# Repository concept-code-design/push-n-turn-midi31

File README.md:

# Push-n-Turn 31

Push-n-Turn 31 is a USB MIDI controller with 3 keyboard switches (RedDragon low profile), a rotary encoder and 3/4 RGB leds (WS8212).

The device sports a USB type-C connector and requires no device drivers on Mac or PC.

The keys can be configured (via MIDI messages, or the configurator) to produce notes, CC codes (momentary or toggle mode). The encoder produces 0..127 on a configurable CC channel. The encoder button produces 127/0 on a CC channel of choice.
Each switch has an RGB led that shows the state of the switch.
The device uses a modified midi library for CH55x devices made by mi:muz 

## Configuring the keys
Configuration of the keys can be done by sending midi codes to the device.
You can use python midiutil for this (https://github.com/sourcebox/midiutil).

start prog
./midiutil.py -d 1 -w 186 102 42

end prog
./midiutil.py -d 1 -w 186 102 43

module type
./midiutil.py -d 1 -w 186 102 44
returns: (10, 103, INSTRUMENT_TYPE);

firmware version
./midiutil.py -d 1 -w 186 102 45
returns (10, 104, FW_VERSION) 10 for version 1.0

show configuration
./midiutil.py -d 1 -w 186 102 46
returns the config of each of the 6 buttons, the rotary knob and rotary encoder

show stepsize 
./midiutil.py -d 1 -w 186 102 47
returns (10, 105, encStepSize)

show MIDI channel 
./midiutil.py -d 1 -w 186 102 48
returns (10, 106, MIDIChannel)

reboot in firmware update mode
./midiutil.py -d 1 -w 186 102 49

programming keys
./midiutil.py -d 1 -w 186 102 42
./midiutil.py -d 1 -w 186 11 60
./midiutil.py -d 1 -w 186 22 30
./midiutil.py -d 1 -w 186 33 9
./midiutil.py -d 1 -w 186 24 15
./midiutil.py -d 1 -w 186 5 24
./midiutil.py -d 1 -w 186 102 43

## Links & References

* [mi:muz:ch55x Tiny USB MIDI Library for Ch55xduino](https://github.com/mimuz/mimuz-ch55x)
* [push-n-turn-midi61](https://github.com/concept-code-design/push-n-turn-midi61)

# License

Concept & Code invests time and resources providing this open source design, please support them and open-source hardware by purchasing products from Etsy or Tindie!

Designed by Ronald Leenes.

Firmware released under an GNU AGPL v3.0 license. See the LICENSE file for more information.

Hardware released under an CERN Open Hardware Licence v1.2. See the LICENSE_HARDWARE file for more information.

February 2025

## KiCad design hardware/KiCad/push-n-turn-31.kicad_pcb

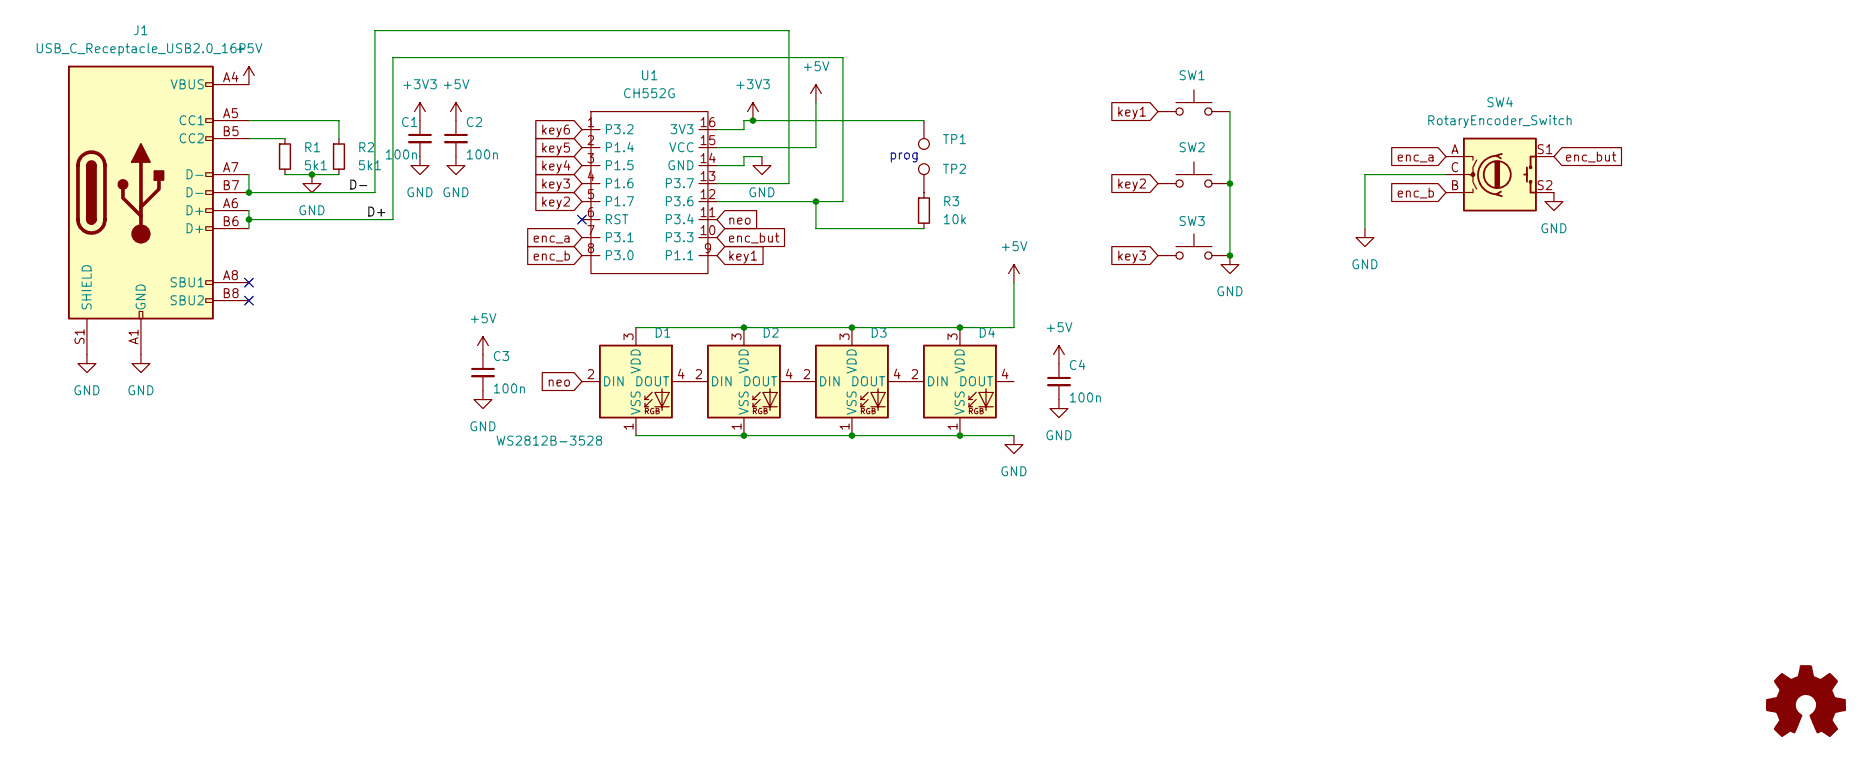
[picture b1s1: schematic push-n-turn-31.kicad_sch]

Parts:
C1, C2, C3, C4: 100n; C_0805_2012Metric
D1, D2, D3, D4: WS2812B-3528; LED_WS2812B-Mini_PLCC4_3.5x2.8mm
J1: USB_C_Receptacle_USB2.0_16P; USB_C_Receptacle_GCT_USB4105-xx-A_16P_TopMnt_Horizontal
R1, R2: 5k1; R_0805_2012Metric
R3: 10k; R_0805_2012Metric
SW1: key1; SW_RedDragon5.5m_Ali_1.00u
SW2: key2; SW_RedDragon5.5m_Ali_1.00u
SW3: key3; SW_RedDragon5.5m_Ali_1.00u
SW4: RotaryEncoder_Switch; RotaryEncoder_Alps_EC12E-Switch_Vertical_H20mm
TP1: TestPoint_Pad_2.5x2.5mm
TP2: TestPoint; TestPoint_Pad_2.5x2.5mm
U1: CH552G; SOP-16_4.4x10.4mm_P1.27mm

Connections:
+3V3: C1.1, TP1.1, U1.16 (3V3)
+5V: C2.1, C3.1, C4.1, D1.3 (VDD), D2.3 (VDD), D3.3 (VDD), D4.3 (VDD), J1.A4 (VBUS), J1.A9 (VBUS), J1.B4 (VBUS), J1.B9 (VBUS), U1.15 (VCC)
/D+: J1.A6 (D+), J1.B6 (D+), R3.2, U1.12 (P3.6)
/D-: J1.A7 (D-), J1.B7 (D-), U1.13 (P3.7)
GND: C1.2, C2.2, C3.2, C4.2, D1.1 (VSS), D2.1 (VSS), D3.1 (VSS), D4.1 (VSS), J1.A1 (GND), J1.A12 (GND), J1.B1 (GND), J1.B12 (GND), J1.S1 (SHIELD), R1.2, R2.2, SW1.2, SW2.2, SW3.2, SW4.C, SW4.S2, U1.14 (GND)
unnamed: D1.4 (DOUT), D2.2 (DIN)
unnamed: D2.4 (DOUT), D3.2 (DIN)
unnamed: D3.4 (DOUT), D4.2 (DIN)
unnamed: J1.A5 (CC1), R2.1
unnamed: J1.B5 (CC2), R1.1
unnamed: R3.1, TP2.1
enc_a: SW4.A, U1.7 (P3.1)
enc_b: SW4.B, U1.8 (P3.0)
enc_but: SW4.S1, U1.10 (P3.3)
key1: SW1.1, U1.9 (P1.1)
key2: SW2.1, U1.5 (P1.7)
key3: SW3.1, U1.4 (P1.6)
key4: U1.3 (P1.5)
key5: U1.2 (P1.4)
key6: U1.1 (P3.2)
neo: D1.2 (DIN), U1.11 (P3.4)

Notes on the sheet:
prog

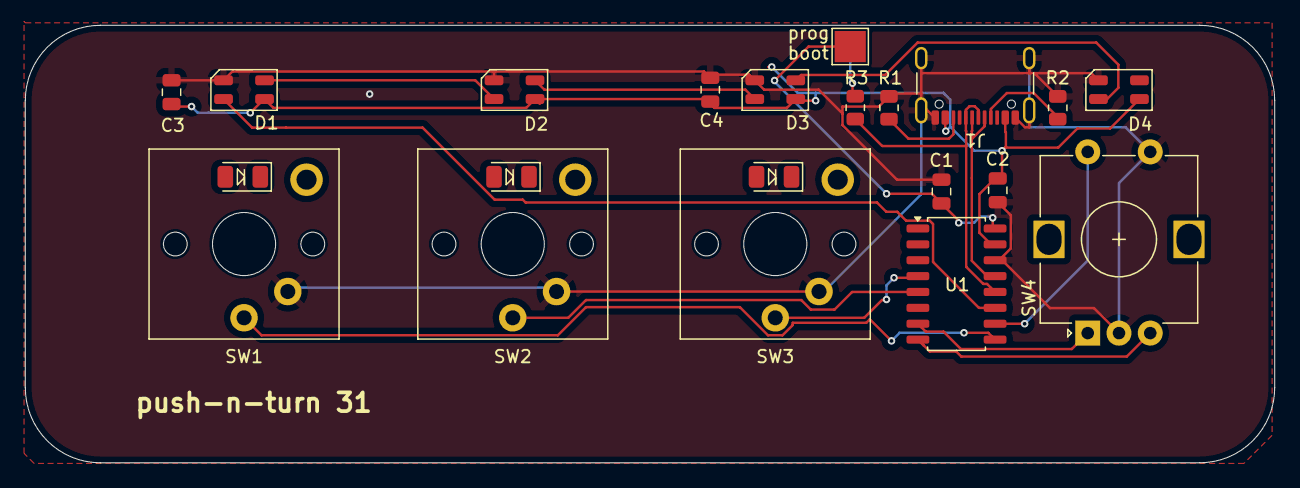
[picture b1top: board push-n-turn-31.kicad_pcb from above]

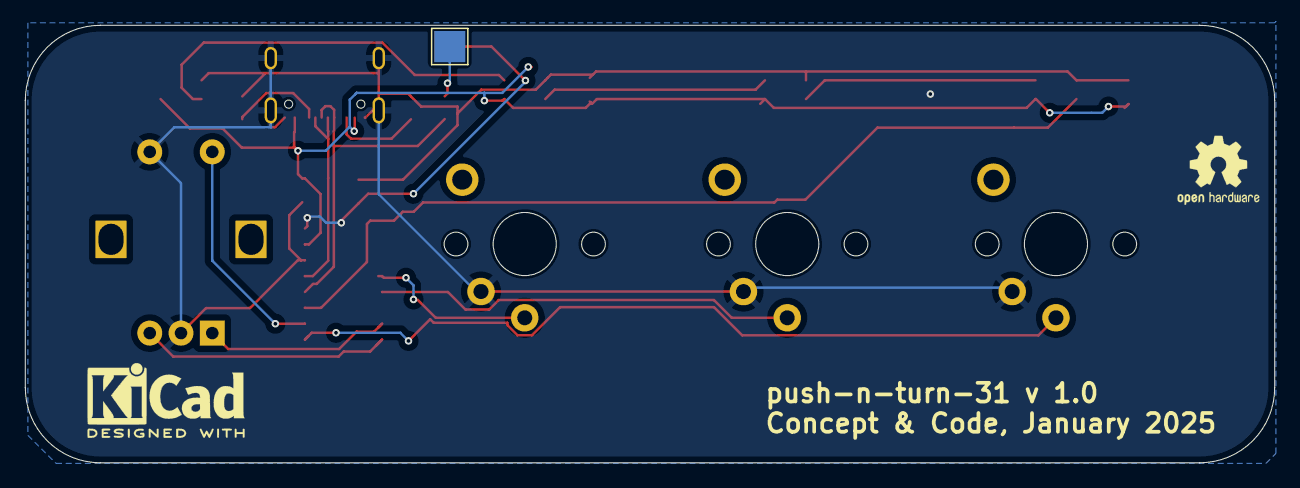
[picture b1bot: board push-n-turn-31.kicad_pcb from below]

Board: 2 copper layers, 100.0 x 35.0 mm, 21 parts (3 on the bottom side), 18 nets.

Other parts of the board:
KICAD: KiCad-Logo2_5mm_SilkScreen
REFOH: OSHW-Logo2_7.3x6mm_SilkScreen

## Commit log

2025-03-03 added firmware
2025-03-03 readme
2025-03-23 fixes
    small fixes
2025-04-26 compiled binaries
2025-05-14 Added KiCad files
